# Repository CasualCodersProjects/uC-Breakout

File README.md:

#  µC USB 2.0 Type C Breakout Board
I like USB C, You like USB C. We all like USB C.  
But there's one thing missing from all the cheap USB Type C breakout boards on the market, and that is support for USB C to C cables.  
This board solves that by following the basic spec and inclusing the two 5k1 pull-down resistors. It also maintains a small and light footprint to make integration easy. Finally, it breaks out all the pins on the type C 2.0 connector, which includes: VCC, GND, D+, D-, CC1, CC2, SBU1, and SBU2.

## Pinout

## Ordering
Download the Gerber.zip in the root of this repository, and ipload it to your board house of choice.  
Assemble using
- 1x Type-C-31-M-12
- 2x 5k1 resistor [package 0402]

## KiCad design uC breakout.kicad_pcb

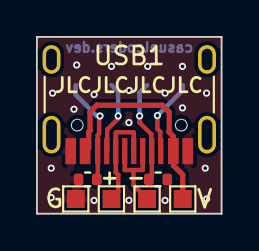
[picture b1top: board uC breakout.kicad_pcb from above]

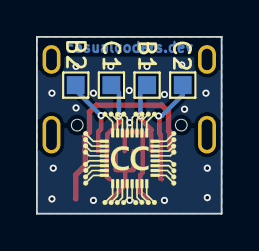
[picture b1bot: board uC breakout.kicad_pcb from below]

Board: 2 copper layers, 10.3 x 9.8 mm, 11 parts (4 on the bottom side), 8 nets.

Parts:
+: TestPoint; TestPoint_Pad_1.0x1.0mm
-: TestPoint; TestPoint_Pad_1.0x1.0mm
B1, B2: TestPoint; TestPoint_Pad_1.0x1.0mm
C1, C2: TestPoint; TestPoint_Pad_1.0x1.0mm
G: TestPoint; TestPoint_Pad_1.0x1.0mm
R1, R2: 5.1k; R_0402_1005Metric
USB1: C-31-M-12; USB_C_Receptacle_HRO_TYPE-C-31-M-12
V: TestPoint; TestPoint_Pad_1.0x1.0mm

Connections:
GND: G.1, R1.1, R2.2, USB1.A1 (GND), USB1.A12 (GND), USB1.B1 (GND), USB1.B12 (GND)
unnamed: USB1.A6 (D+), USB1.B6 (D+)
unnamed: USB1.A7 (D-), USB1.B7 (D-)
unnamed: B1.1, USB1.A8 (SBU1)
unnamed: B2.1, USB1.B8 (SBU2)
unnamed: C1.1, R1.2, USB1.A5 (CC1)
unnamed: C2.1, R2.1, USB1.B5 (CC2)
VCC: USB1.A4 (VBUS), USB1.A9 (VBUS), USB1.B4 (VBUS), USB1.B9 (VBUS), V.1

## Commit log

2023-08-25 Added design files
2023-08-25 Generate Gerbers
2023-08-25 Add readme
